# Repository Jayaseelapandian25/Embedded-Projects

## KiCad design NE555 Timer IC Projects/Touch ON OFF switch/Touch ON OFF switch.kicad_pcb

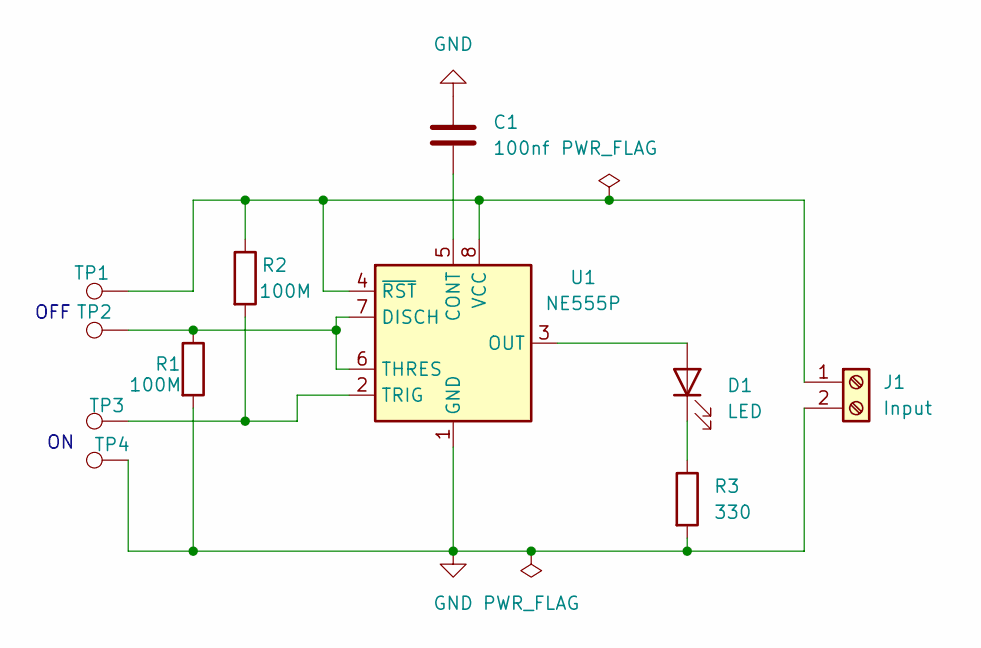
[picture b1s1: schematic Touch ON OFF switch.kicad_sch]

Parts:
C1: 100nf; C_Disc_D5.0mm_W2.5mm_P5.00mm
D1: LED; LED_D5.0mm
J1: Input; TerminalBlock_MaiXu_MX126-5.0-02P_1x02_P5.00mm
R1, R2: 100M; R_Axial_DIN0207_L6.3mm_D2.5mm_P7.62mm_Horizontal
R3: 330; R_Axial_DIN0207_L6.3mm_D2.5mm_P7.62mm_Horizontal
TP1, TP2, TP3, TP4: TestPoint; TestPoint_Pad_D4.0mm
U1: NE555P; DIP-8_W7.62mm

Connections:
GND: C1.1, J1.2, R1.2, R3.2, TP4.1 (1_1), U1.1 (GND)
unnamed: D1.2 (A), U1.3 (OUT)
unnamed: D1.1 (K), R3.1
unnamed: J1.1, R2.1, TP1.1 (1_1), U1.4 (~RST), U1.8 (VCC)
unnamed: C1.2, U1.5 (CONT)
unnamed: R1.1, TP2.1 (1_1), U1.6 (THRES), U1.7 (DISCH)
unnamed: R2.2, TP3.1 (1_1), U1.2 (TRIG)

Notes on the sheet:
OFF

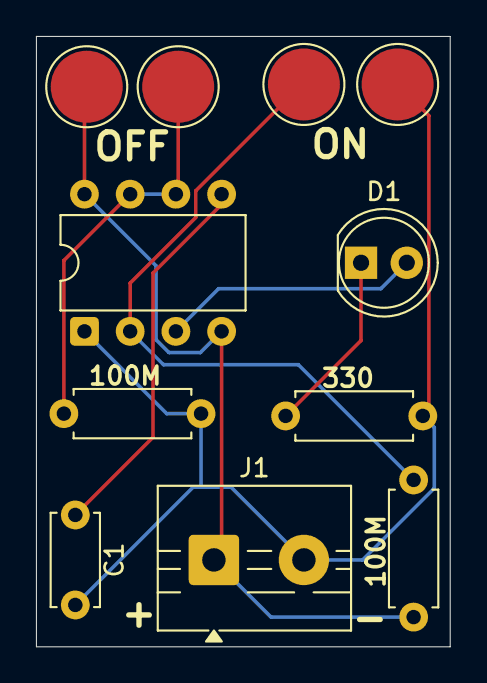
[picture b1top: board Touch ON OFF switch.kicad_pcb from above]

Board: 2 copper layers, 23.0 x 33.9 mm, 11 parts (0 on the bottom side), 7 nets.

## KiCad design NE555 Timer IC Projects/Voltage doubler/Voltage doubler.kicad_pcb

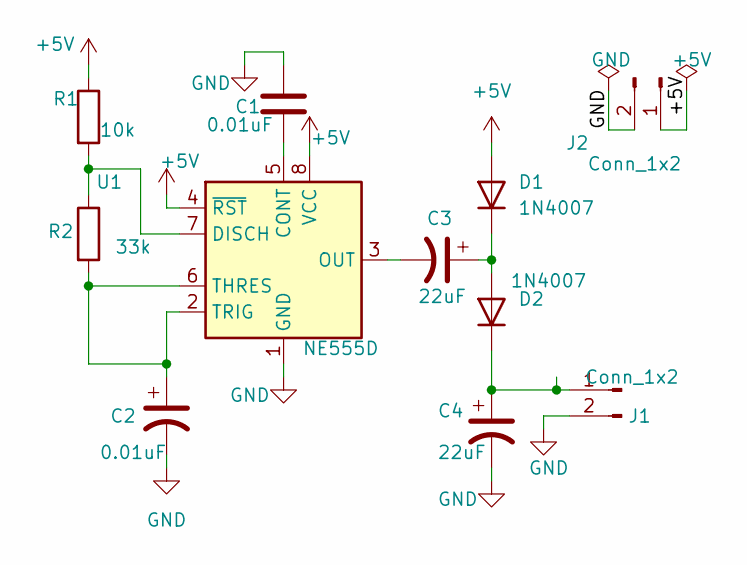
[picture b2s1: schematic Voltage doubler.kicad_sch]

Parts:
C1, C2: 0.01uF; C_Disc_D3.0mm_W1.6mm_P2.50mm
C3, C4: 22uF; C_Radial_D4.0mm_H5.0mm_P1.50mm
D1, D2: 1N4007; D_5W_P10.16mm_Horizontal
J1, J2: Conn_1x2; PinHeader_1x02_P1.00mm_Horizontal
R1: 10k; R_Axial_DIN0204_L3.6mm_D1.6mm_P5.08mm_Horizontal
R2: 33k; R_Axial_DIN0204_L3.6mm_D1.6mm_P5.08mm_Horizontal
U1: NE555D; SO-8_3.9x4.9mm_P1.27mm

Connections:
+5V: D1.2 (A), J2.1, R1.1, U1.4 (~RST), U1.8 (VCC)
GND: C1.1, C2.2, C4.2, J1.2, J2.2, U1.1 (GND)
unnamed: C3.1, D1.1 (K), D2.2 (A)
unnamed: C4.1, D2.1 (K), J1.1
unnamed: C1.2, U1.5 (CONT)
unnamed: R1.2, R2.1, U1.7 (DISCH)
unnamed: C3.2, U1.3 (OUT)
unnamed: C2.1, R2.2, U1.2 (TRIG), U1.6 (THRES)

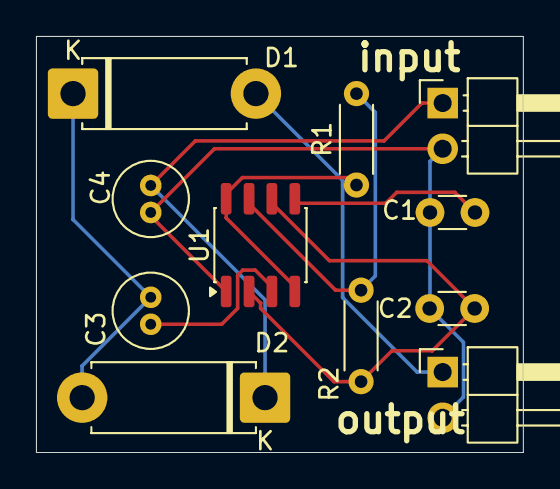
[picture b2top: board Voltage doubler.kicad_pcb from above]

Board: 2 copper layers, 27.1 x 23.1 mm, 11 parts (0 on the bottom side), 8 nets.

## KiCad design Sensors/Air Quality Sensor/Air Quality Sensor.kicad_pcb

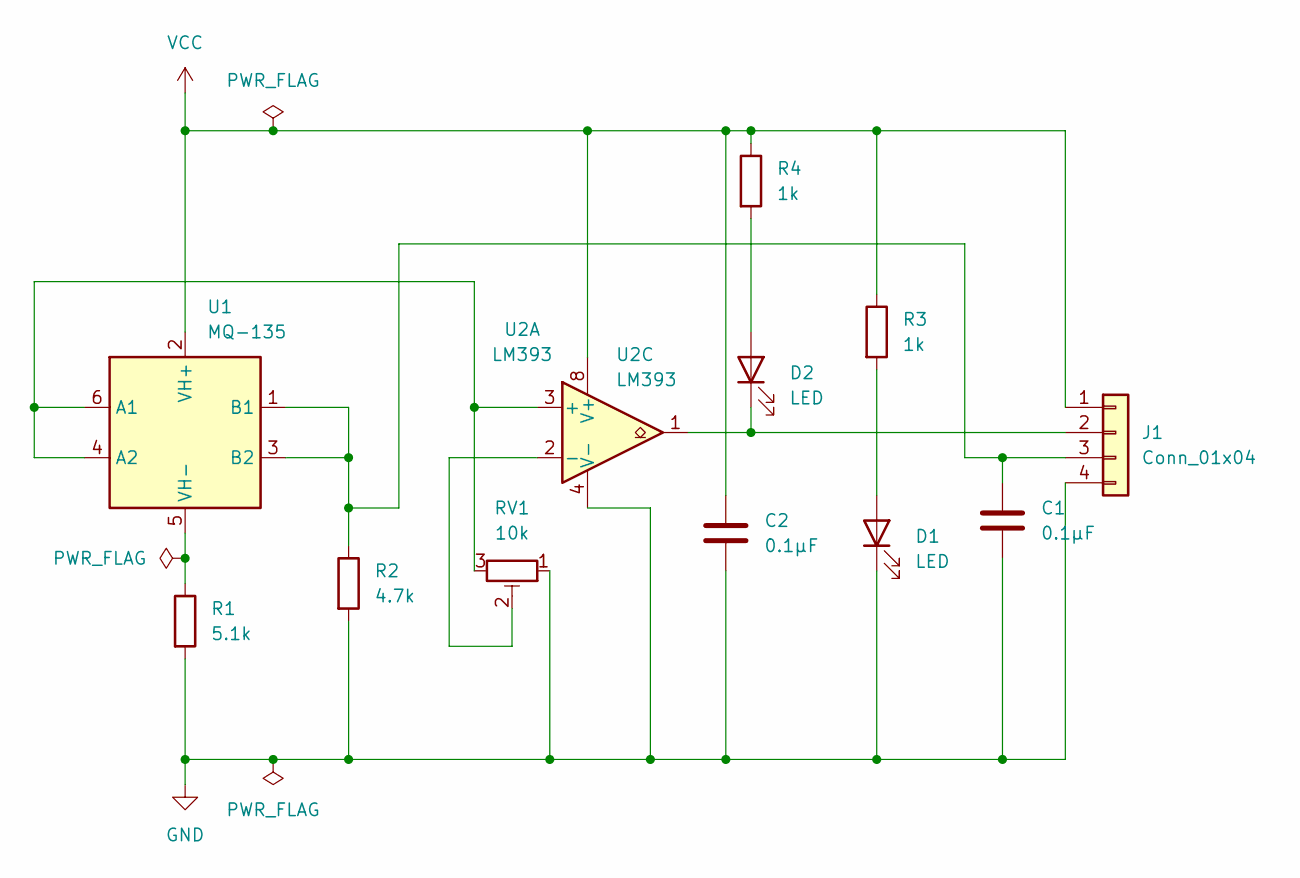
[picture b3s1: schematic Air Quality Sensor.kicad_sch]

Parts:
C1, C2: 0.1µF; C_0805_2012Metric_Pad1.18x1.45mm_HandSolder
D1, D2: LED; LED_0805_2012Metric_Pad1.15x1.40mm_HandSolder
J1: Conn_01x04; PinHeader_1x04_P2.54mm_Vertical
R1: 5.1k; R_0805_2012Metric_Pad1.20x1.40mm_HandSolder
R2: 4.7k; R_0805_2012Metric_Pad1.20x1.40mm_HandSolder
R3, R4: 1k; R_0805_2012Metric_Pad1.20x1.40mm_HandSolder
RV1: 10k; Potentiometer_Bourns_3214X_Vertical
U1: MQ-135; MQ-6
U2: LM393; SOIC-8_3.9x4.9mm_P1.27mm

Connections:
GND: C1.2, C2.2, D1.1 (K), J1.4, R1.2, R2.2, RV1.1, U2.4 (V-)
unnamed: D1.2 (A), R3.2
unnamed: D2.2 (A), R4.2
unnamed: D2.1 (K), J1.2, U2.1
unnamed: C1.1, J1.3, R2.1, U1.1 (B1), U1.3 (B2)
unnamed: RV1.3, U1.4 (A2), U1.6 (A1), U2.3 (+)
unnamed: R1.1, U1.5 (VH-)
unnamed: RV1.2, U2.2 (-)
VCC: C2.1, J1.1, R3.1, R4.1, U1.2 (VH+), U2.8 (V+)

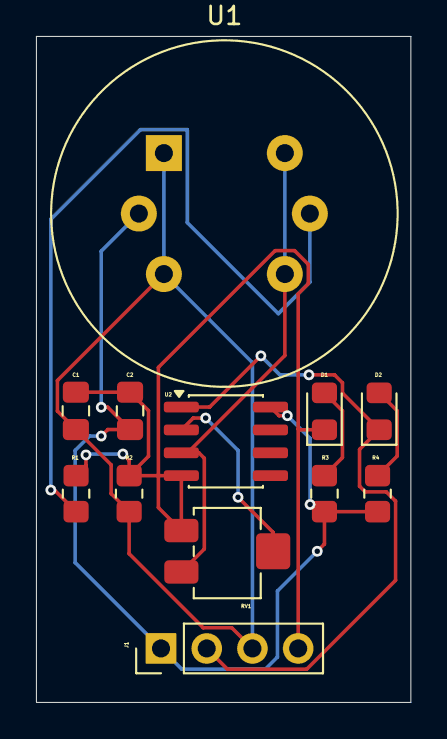
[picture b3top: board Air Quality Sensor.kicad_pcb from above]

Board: 2 copper layers, 20.8 x 37.0 mm, 12 parts (0 on the bottom side), 9 nets.

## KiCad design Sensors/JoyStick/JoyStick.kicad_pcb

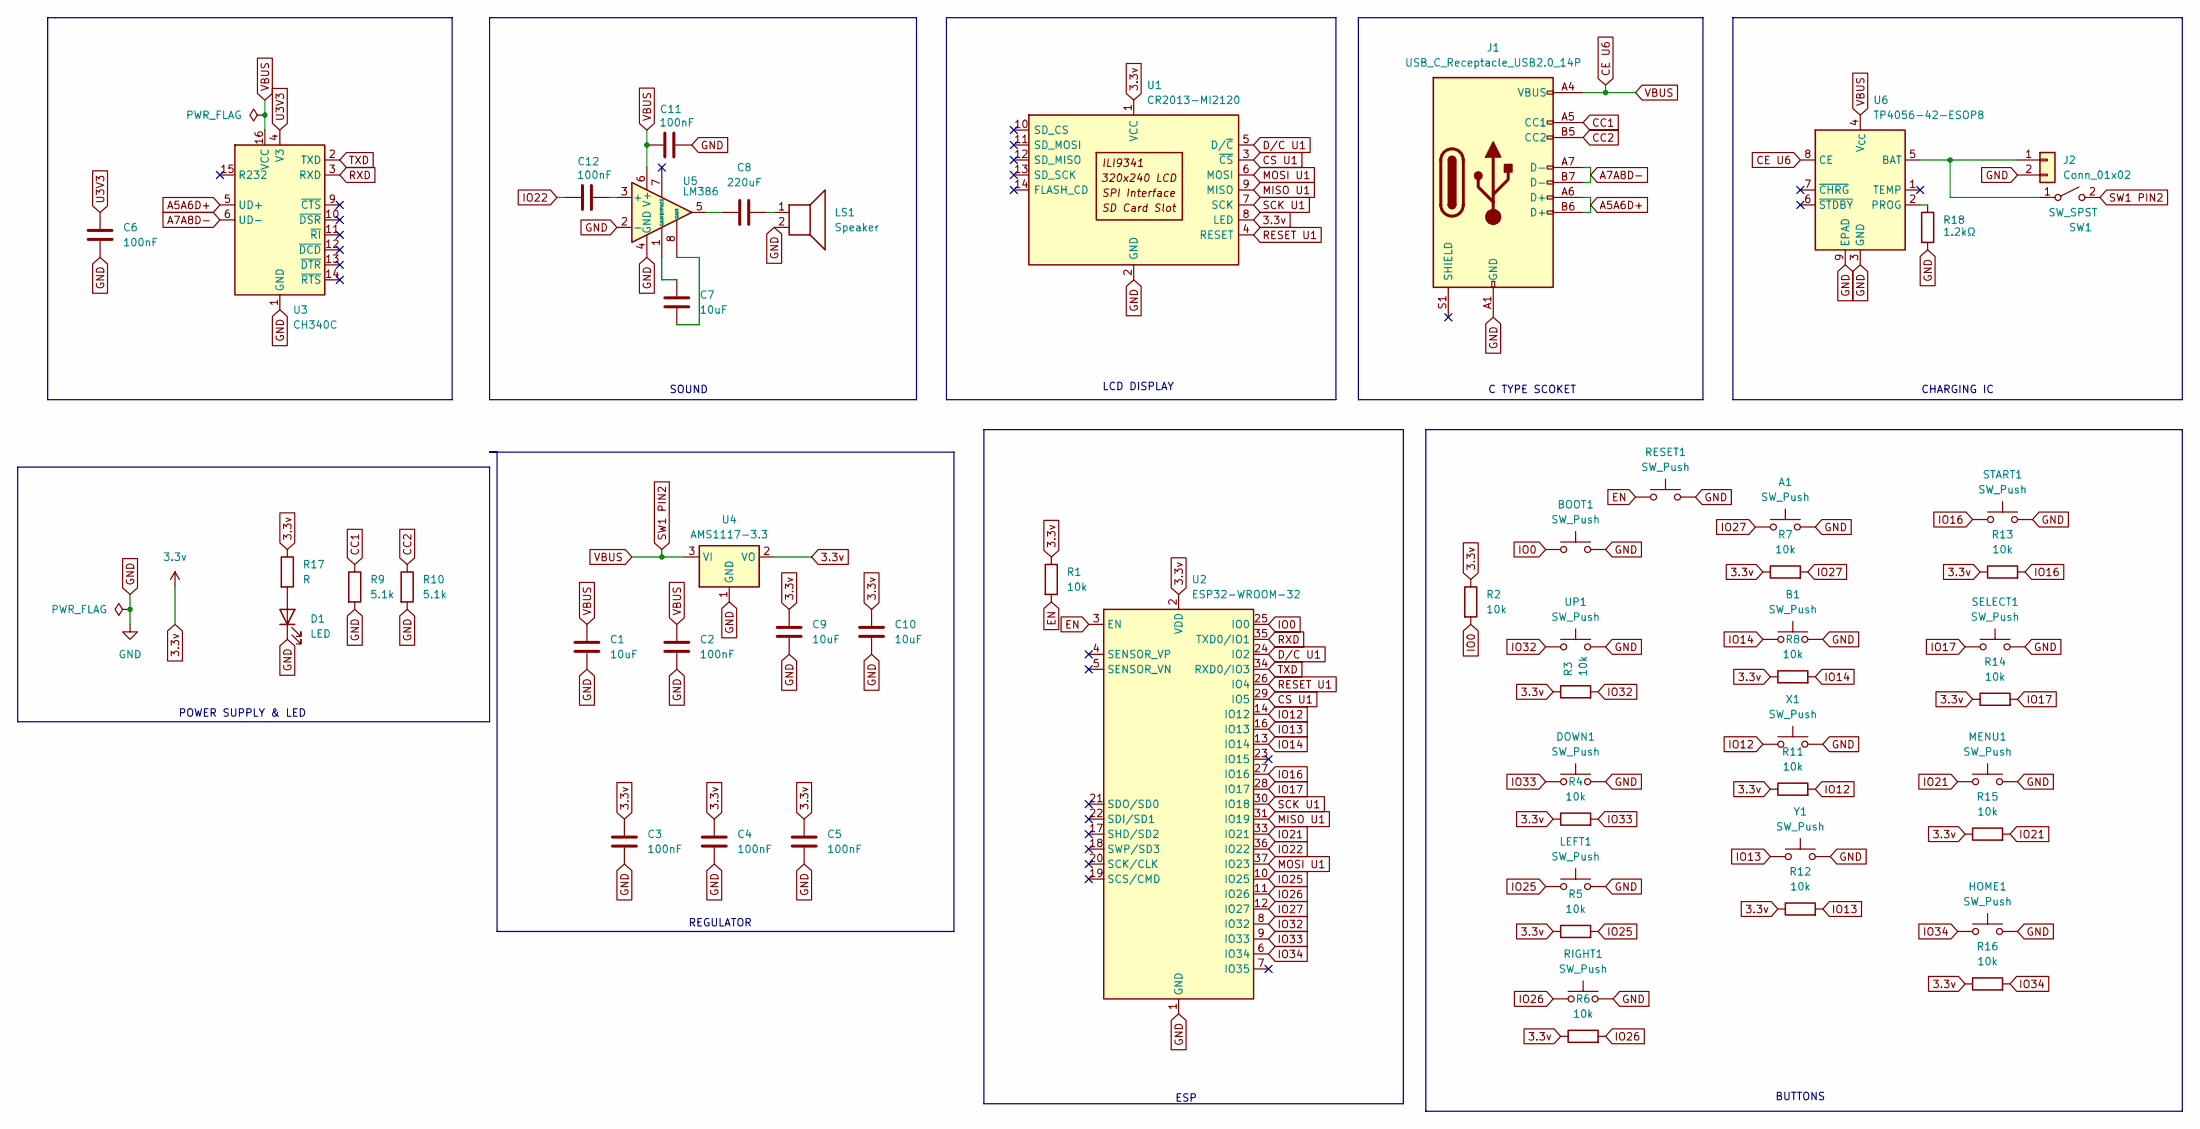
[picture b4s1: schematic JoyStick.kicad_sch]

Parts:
A1: SW_Push; SW_SPST_TL3342
B1: SW_Push; SW_SPST_TL3342
BOOT1: SW_Push; SW_SPST_TL3342
C1, C7, C9, C10: 10uF; C_0805_2012Metric
C2, C3, C4, C5, C6, C11, C12: 100nF; C_0805_2012Metric
C8: 220uF; C_0805_2012Metric
D1: LED; LED_0805_2012Metric
DOWN1: SW_Push; SW_SPST_TL3342
HOME1: SW_Push; SW_SPST_TL3342
J1: USB_C_Receptacle_USB2.0_14P; USB_C_Receptacle_HRO_TYPE-C-31-M-12
J2: Conn_01x02; JST_PH_S2B-PH-K_1x02_P2.00mm_Horizontal
LEFT1: SW_Push; SW_SPST_TL3342
LS1: Speaker; JST_PH_S2B-PH-K_1x02_P2.00mm_Horizontal
MENU1: SW_Push; SW_SPST_TL3342
R1, R2, R3, R4, R5, R6, R7, R8, R11, R12, R13, R14, R15, R16: 10k; R_0805_2012Metric
R9, R10: 5.1k; R_0805_2012Metric
R17: R; R_0805_2012Metric
R18: 1.2kΩ; R_0805_2012Metric
RESET1: SW_Push; SW_SPST_TL3342
RIGHT1: SW_Push; SW_SPST_TL3342
SELECT1: SW_Push; SW_SPST_TL3342
START1: SW_Push; SW_SPST_TL3342
SW1: SW_SPST; SW_SPST_TL3342
U1: CR2013-MI2120
U2: ESP32-WROOM-32
U3: CH340C; SOIC-16_3.9x9.9mm_P1.27mm
U4: AMS1117-3.3; SOT-223-3_TabPin2
U5: LM386; SOIC-8_3.9x4.9mm_P1.27mm
U6: TP4056-42-ESOP8; SOIC-8-1EP_3.9x4.9mm_P1.27mm_EP2.41x3.3mm_ThermalVias
UP1: SW_Push; SW_SPST_TL3342
X1: SW_Push; SW_SPST_TL3342
Y1: SW_Push; SW_SPST_TL3342

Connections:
3.3v: C3.1, C4.1, C5.1, C9.1, C10.1, R1.1, R2.1, R3.1, R4.1, R5.1, R6.1, R7.1, R8.1, R11.1, R12.1, R13.1, R14.1, R15.1, R16.1, R17.1, U1.1 (VCC), U1.8 (LED), U2.2 (VDD), U4.2 (VO)
A5A6D+: J1.A6 (D+), J1.B6 (D+), U3.5 (UD+)
A7A8D-: J1.A7 (D-), J1.B7 (D-), U3.6 (UD-)
CC1: J1.A5 (CC1), R9.1
CC2: J1.B5 (CC2), R10.1
CE U6: C1.1, C2.1, C11.1, J1.A4 (VBUS), J1.A9 (VBUS), J1.B4 (VBUS), J1.B9 (VBUS), SW1.2 (B), U3.16 (VCC), U4.3 (VI), U5.6 (V+), U6.4 (V_{CC}), U6.8 (CE)
CS U1: U1.3 (~CS), U2.29 (IO5)
D/C U1: U1.5 (D/~C), U2.24 (IO2)
EN: R1.2, RESET1.1, U2.3 (EN)
GND: A1.2, B1.2, BOOT1.2, C1.2, C2.2, C3.2, C4.2, C5.2, C6.2, C9.2, C10.2, C11.2, D1.1 (K), DOWN1.2, HOME1.2, J1.A1 (GND), J1.A12 (GND), J1.B1 (GND), J1.B12 (GND), J2.2, LEFT1.2, LS1.2, MENU1.2, R9.2, R10.2, R18.2, RESET1.2, RIGHT1.2, SELECT1.2, START1.2, U1.2 (GND), U2.1 (GND), U2.15 (GND), U2.38 (GND), U2.39 (GND), U3.1 (GND), U4.1 (GND), U5.2 (-), U5.4 (GND), U6.3 (GND), U6.9 (EPAD), UP1.2, X1.2, Y1.2
IO0: BOOT1.1, R2.2, U2.25 (IO0)
IO12: R11.2, U2.14 (IO12), X1.1
IO13: R12.2, U2.16 (IO13), Y1.1
IO14: B1.1, R8.2, U2.13 (IO14)
IO16: R13.2, START1.1, U2.27 (IO16)
IO17: R14.2, SELECT1.1, U2.28 (IO17)
IO21: MENU1.1, R15.2, U2.33 (IO21)
IO22: C12.1, U2.36 (IO22)
IO25: LEFT1.1, R5.2, U2.10 (IO25)
IO26: R6.2, RIGHT1.1, U2.11 (IO26)
IO27: A1.1, R7.2, U2.12 (IO27)
IO32: R3.2, U2.8 (IO32), UP1.1
IO33: DOWN1.1, R4.2, U2.9 (IO33)
IO34: HOME1.1, R16.2, U2.6 (IO34)
MISO U1: U1.9 (MISO), U2.31 (IO19)
MOSI U1: U1.6 (MOSI), U2.37 (IO23)
unnamed: C7.1, U5.1 (GAIN)
unnamed: C7.2, U5.8 (GAIN)
unnamed: C8.1, U5.5
unnamed: C8.2, LS1.1
unnamed: D1.2 (A), R17.2
unnamed: J2.1, SW1.1 (A), U6.5 (BAT)
unnamed: C12.2, U5.3 (+)
unnamed: R18.1, U6.2 (PROG)
RESET U1: U1.4 (RESET), U2.26 (IO4)
RXD: U2.35 (TXD0/IO1), U3.3 (RXD)
SCK U1: U1.7 (SCK), U2.30 (IO18)
TXD: U2.34 (RXD0/IO3), U3.2 (TXD)
U3V3: C6.1, U3.4 (V3)

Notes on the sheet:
CHARGING IC
LCD DISPLAY
SOUND
POWER SUPPLY & LED
BUTTONS
C TYPE SCOKET
ESP
REGULATOR

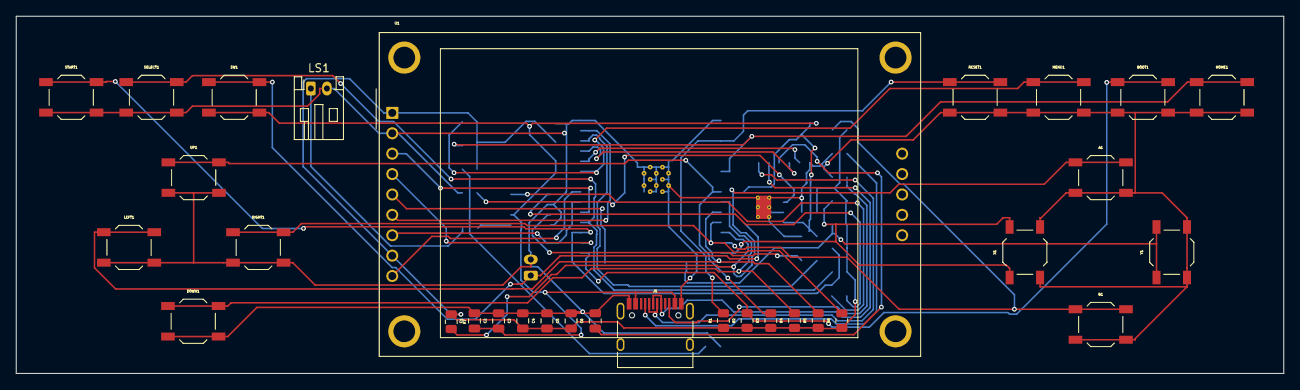
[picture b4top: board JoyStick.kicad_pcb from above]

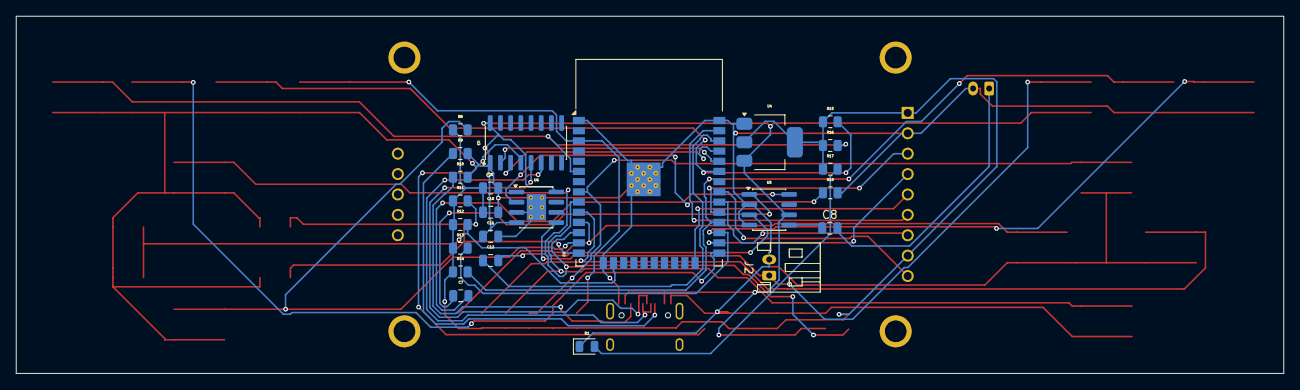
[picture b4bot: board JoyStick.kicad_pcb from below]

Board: 2 copper layers, 157.9 x 44.5 mm, 55 parts (24 on the bottom side), 39 nets.

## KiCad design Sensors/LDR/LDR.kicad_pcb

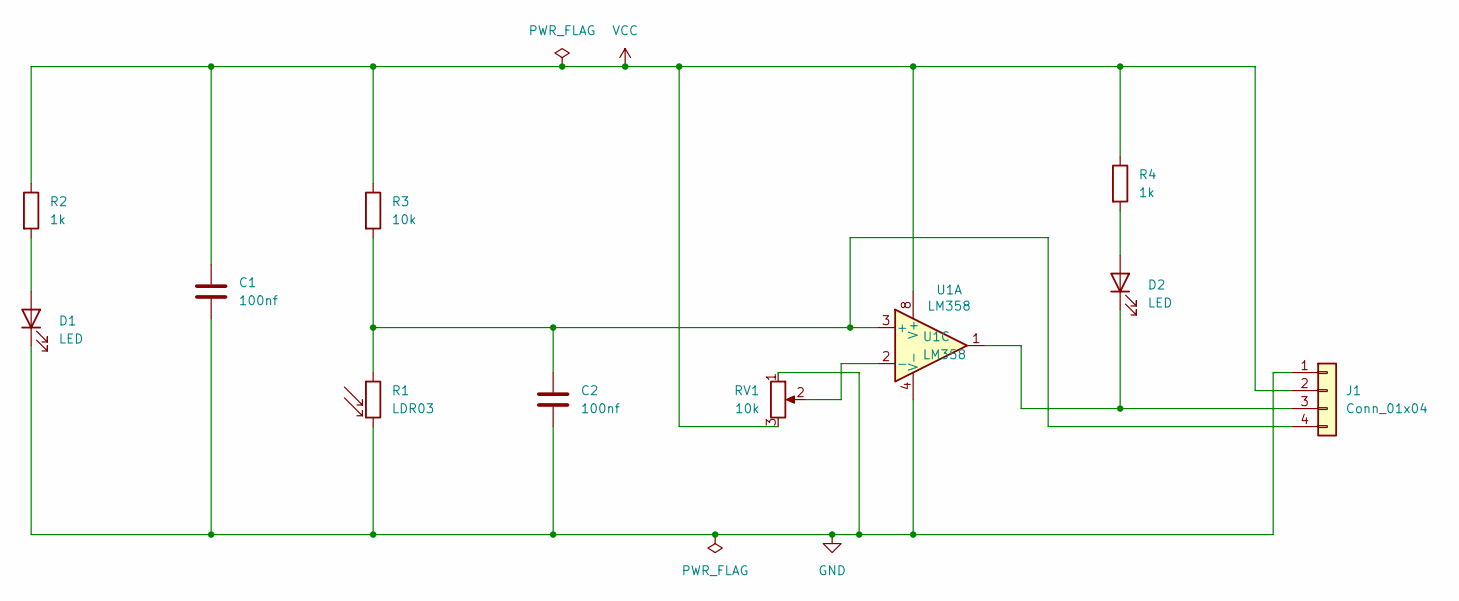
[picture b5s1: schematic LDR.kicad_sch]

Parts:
C1, C2: 100nf; C_0805_2012Metric_Pad1.18x1.45mm_HandSolder
D1, D2: LED; LED_0805_2012Metric_Pad1.15x1.40mm_HandSolder
J1: Conn_01x04; PinHeader_1x04_P2.54mm_Vertical
R1: LDR03; R_LDR_10x8.5mm_P7.6mm_Vertical
R2, R4: 1k; R_0805_2012Metric_Pad1.20x1.40mm_HandSolder
R3: 10k; R_0805_2012Metric_Pad1.20x1.40mm_HandSolder
RV1: 10k; Potentiometer_Bourns_3296W_Vertical
U1: LM358; DIP-8_W7.62mm

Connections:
GND: C1.2, C2.2, D1.1 (K), J1.1, R1.2, RV1.1, U1.4 (V-)
unnamed: D1.2 (A), R2.2
unnamed: D2.2 (A), R4.2
unnamed: D2.1 (K), J1.3, U1.1
unnamed: C2.1, J1.4, R1.1, R3.2, U1.3 (+)
unnamed: RV1.2, U1.2 (-)
VCC: C1.1, J1.2, R2.1, R3.1, R4.1, RV1.3, U1.8 (V+)

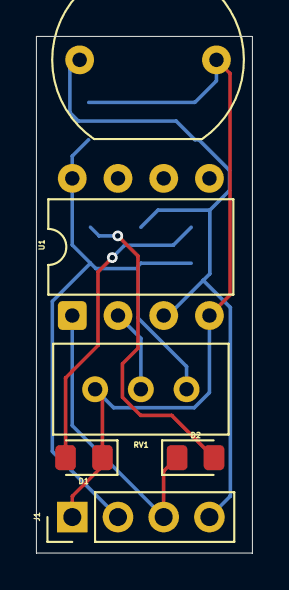
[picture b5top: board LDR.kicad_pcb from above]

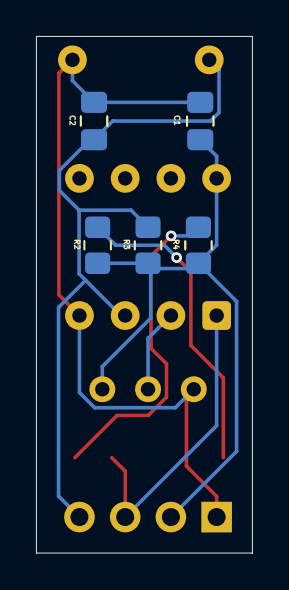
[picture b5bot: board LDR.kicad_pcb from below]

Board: 2 copper layers, 12.0 x 28.7 mm, 11 parts (5 on the bottom side), 7 nets.

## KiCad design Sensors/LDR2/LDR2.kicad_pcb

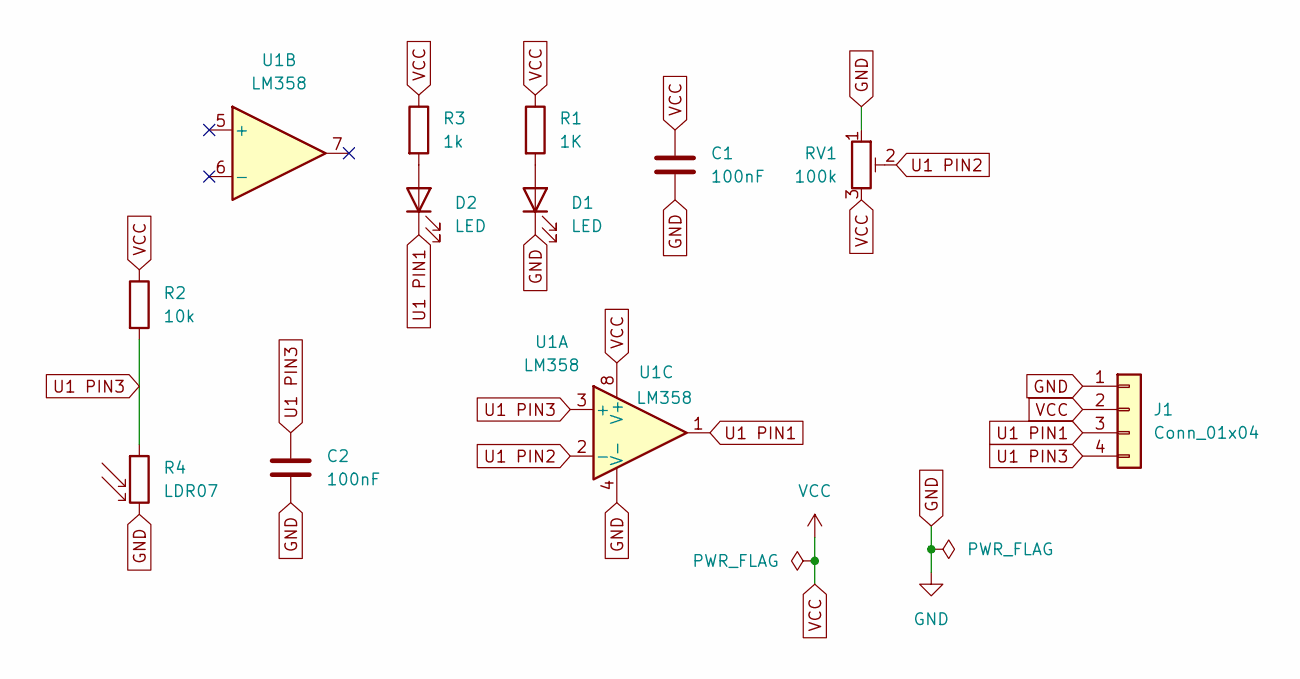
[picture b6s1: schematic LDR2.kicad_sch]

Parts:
C1, C2: 100nF; C_0805_2012Metric_Pad1.18x1.45mm_HandSolder
D1, D2: LED; LED_0805_2012Metric_Pad1.15x1.40mm_HandSolder
J1: Conn_01x04; PinHeader_1x04_P2.54mm_Vertical
R1: 1K; R_0805_2012Metric_Pad1.20x1.40mm_HandSolder
R2: 10k; R_0805_2012Metric_Pad1.20x1.40mm_HandSolder
R3: 1k; R_0805_2012Metric_Pad1.20x1.40mm_HandSolder
R4: LDR07; R_LDR_5.1x4.3mm_P3.4mm_Vertical
RV1: 100k; Potentiometer_Bourns_3296W_Vertical
U1: LM358; DIP-8_W7.62mm

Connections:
GND: C1.2, C2.2, D1.1 (K), J1.1, R4.2, RV1.1, U1.4 (V-)
unnamed: D1.2 (A), R1.2
unnamed: D2.2 (A), R3.2
U1 PIN1: D2.1 (K), J1.3, U1.1
U1 PIN2: RV1.2, U1.2 (-)
U1 PIN3: C2.1, J1.4, R2.2, R4.1, U1.3 (+)
VCC: C1.1, J1.2, R1.1, R2.1, R3.1, RV1.3, U1.8 (V+)

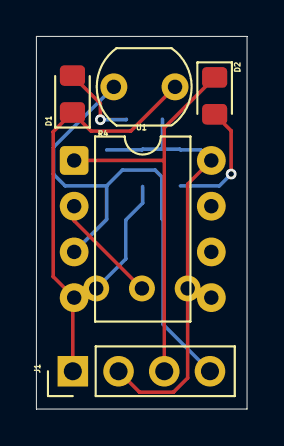
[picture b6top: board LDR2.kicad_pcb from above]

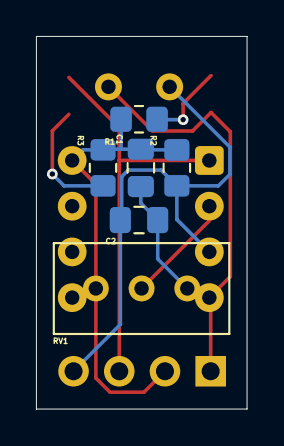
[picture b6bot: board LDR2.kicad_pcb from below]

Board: 2 copper layers, 11.7 x 20.7 mm, 11 parts (6 on the bottom side), 7 nets.

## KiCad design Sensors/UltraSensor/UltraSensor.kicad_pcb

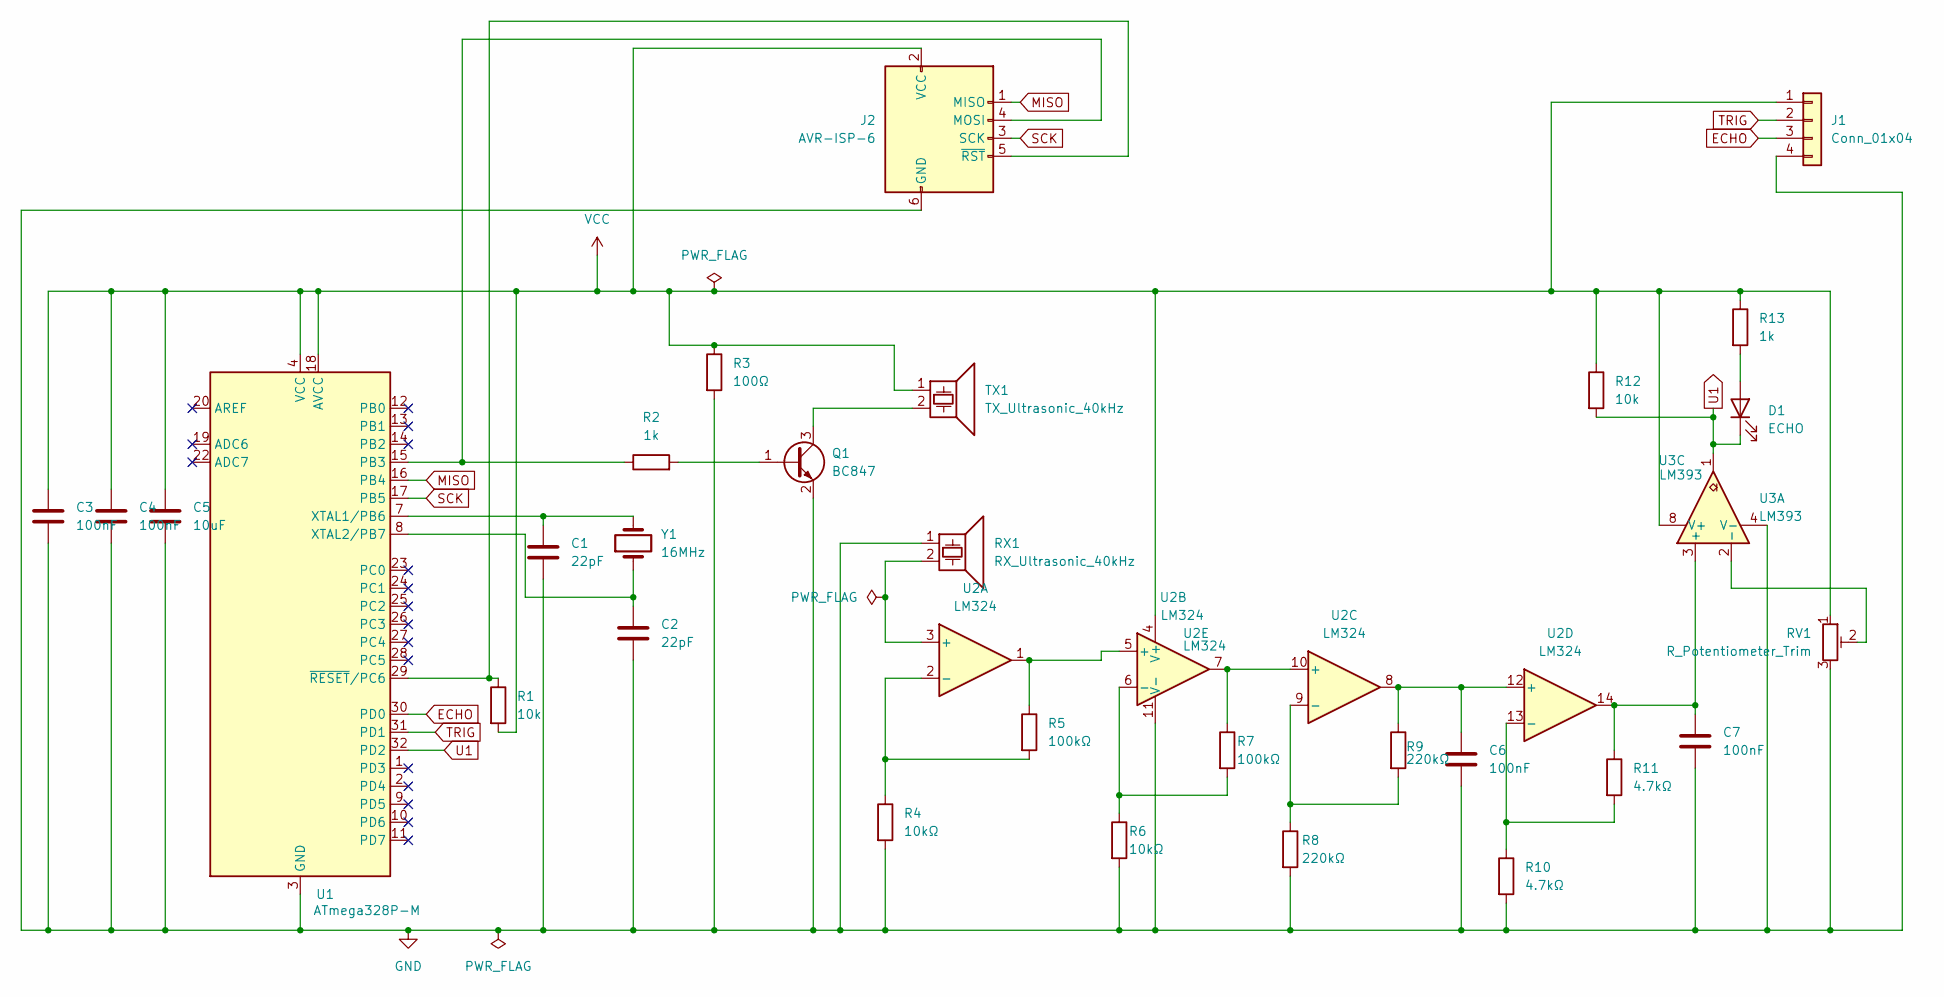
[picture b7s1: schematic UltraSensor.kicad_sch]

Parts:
C1, C2: 22pF; C_0805_2012Metric_Pad1.18x1.45mm_HandSolder
C3, C4, C6, C7: 100nF; C_0805_2012Metric_Pad1.18x1.45mm_HandSolder
C5: 10uF; C_0805_2012Metric_Pad1.18x1.45mm_HandSolder
D1: ECHO; LED_0805_2012Metric
J1: Conn_01x04; PinHeader_1x04_P2.54mm_Vertical
J2: AVR-ISP-6; PinHeader_2x03_P2.54mm_Vertical
Q1: BC847; SOT-23
R1, R12: 10k; R_0805_2012Metric_Pad1.20x1.40mm_HandSolder
R2, R13: 1k; R_0805_2012Metric_Pad1.20x1.40mm_HandSolder
R3: 100Ω; R_0805_2012Metric_Pad1.20x1.40mm_HandSolder
R4, R6: 10kΩ; R_0805_2012Metric_Pad1.20x1.40mm_HandSolder
R5, R7: 100kΩ; R_0805_2012Metric_Pad1.20x1.40mm_HandSolder
R8, R9: 220kΩ; R_0805_2012Metric_Pad1.20x1.40mm_HandSolder
R10, R11: 4.7kΩ; R_0805_2012Metric_Pad1.20x1.40mm_HandSolder
RV1: R_Potentiometer_Trim; Potentiometer_ACP_CA6-VSMD_Vertical
RX1: RX_Ultrasonic_40kHz; Buzzer_12x9.5RM7.6
TX1: TX_Ultrasonic_40kHz; Buzzer_12x9.5RM7.6
U1: ATmega328P-M; QFN-32-1EP_5x5mm_P0.5mm_EP3.1x3.1mm
U2: LM324; SOIC-14_3.9x8.7mm_P1.27mm
U3: LM393; SOIC-8_3.9x4.9mm_P1.27mm
Y1: 16MHz; Crystal_SMD_3225-4Pin_3.2x2.5mm_HandSoldering

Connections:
ECHO: J1.3, U1.30 (PD0)
GND: C1.2, C2.2, C3.2, C4.2, C5.2, C6.2, C7.2, J1.4, J2.6 (GND), Q1.2 (E), R3.2, R4.2, R6.2, R8.2, R10.2, RV1.3, RX1.1, U1.3 (GND), U1.5 (GND), U1.21 (GND), U1.33 (GND), U2.11 (V-), U3.4 (V-)
MISO: J2.1 (MISO), U1.16 (PB4)
unnamed: D1.2 (A), R13.2
unnamed: J2.4 (MOSI), R2.1, U1.15 (PB3)
unnamed: J2.5 (~RST), R1.1, U1.29 (~RESET/PC6)
unnamed: Q1.1 (B), R2.2
unnamed: Q1.3 (C), TX1.2
unnamed: C1.1, U1.7 (XTAL1/PB6), Y1.2
unnamed: C2.1, U1.8 (XTAL2/PB7), Y1.1
unnamed: RX1.2, U2.3 (+)
unnamed: R4.1, R5.2, U2.2 (-)
unnamed: R5.1, U2.1, U2.5 (+)
unnamed: R6.1, R7.2, U2.6 (-)
unnamed: R7.1, U2.7, U2.10 (+)
unnamed: R8.1, R9.2, U2.9 (-)
unnamed: C6.1, R9.1, U2.8, U2.12 (+)
unnamed: R10.1, R11.2, U2.13 (-)
unnamed: C7.1, R11.1, U2.14, U3.3 (+)
unnamed: RV1.2, U3.2 (-)
SCK: J2.3 (SCK), U1.17 (PB5)
TRIG: J1.2, U1.31 (PD1)
U1: D1.1 (K), R12.2, U1.32 (PD2), U3.1
VCC: C3.1, C4.1, C5.1, J1.1, J2.2 (VCC), R1.2, R3.1, R12.1, R13.1, RV1.1, TX1.1, U1.4 (VCC), U1.6 (VCC), U1.18 (AVCC), U2.4 (V+), U3.8 (V+)

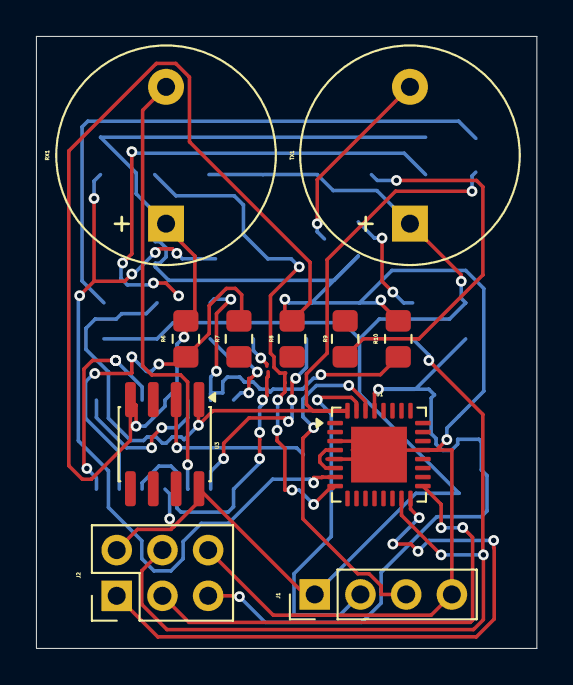
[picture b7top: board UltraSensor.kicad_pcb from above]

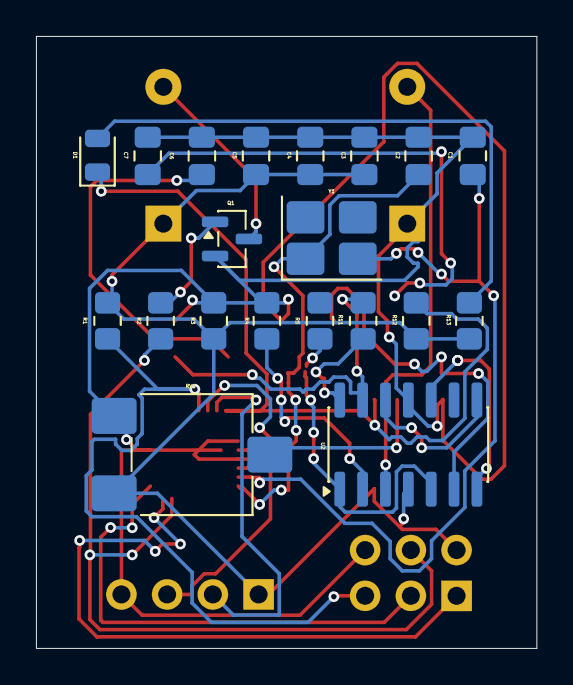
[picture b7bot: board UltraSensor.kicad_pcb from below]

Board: 2 copper layers, 27.8 x 34.0 mm, 31 parts (20 on the bottom side), 24 nets.

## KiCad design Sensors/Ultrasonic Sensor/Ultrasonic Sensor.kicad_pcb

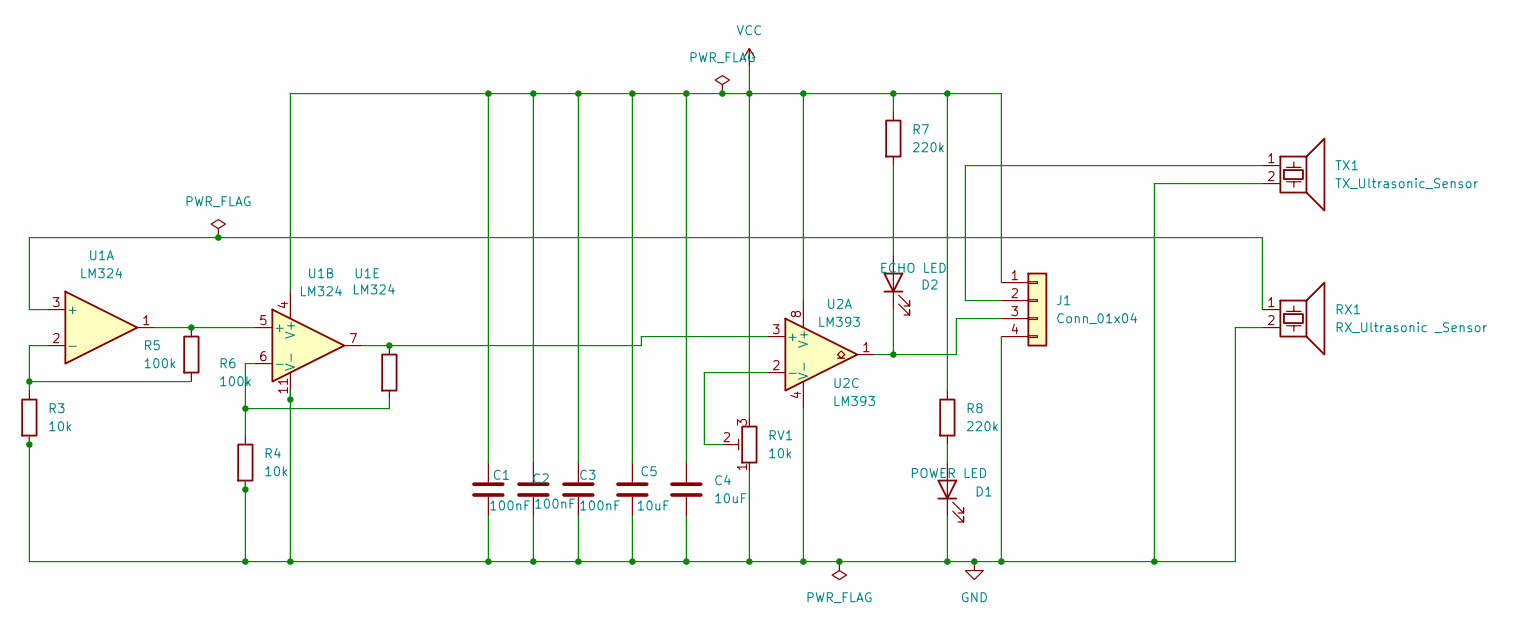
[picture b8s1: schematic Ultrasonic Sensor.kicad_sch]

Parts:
C1, C2, C3: 100nF; C_0805_2012Metric_Pad1.18x1.45mm_HandSolder
C4, C5: 10uF; C_0805_2012Metric_Pad1.18x1.45mm_HandSolder
D1: POWER LED; LED_0805_2012Metric_Pad1.15x1.40mm_HandSolder
D2: ECHO LED; LED_0805_2012Metric_Pad1.15x1.40mm_HandSolder
J1: Conn_01x04; PinHeader_1x04_P2.54mm_Vertical
R3, R4: 10k; R_0805_2012Metric_Pad1.20x1.40mm_HandSolder
R5, R6: 100k; R_0805_2012Metric_Pad1.20x1.40mm_HandSolder
R7, R8: 220k; R_0805_2012Metric_Pad1.20x1.40mm_HandSolder
RV1: 10k; Potentiometer_Bourns_3214X_Vertical
RX1: RX_Ultrasonic _Sensor; Buzzer_12x9.5RM7.6
TX1: TX_Ultrasonic_Sensor; Buzzer_12x9.5RM7.6
U1: LM324; SOIC-14_3.9x8.7mm_P1.27mm
U2: LM393; SOIC-8_3.9x4.9mm_P1.27mm

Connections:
GND: C1.2, C2.2, C3.2, C4.2, C5.2, D1.1 (K), J1.4, R3.2, R4.2, RV1.1, RX1.2, TX1.2, U1.11 (V-), U2.4 (V-)
unnamed: D1.2 (A), R8.2
unnamed: D2.2 (A), R7.2
unnamed: D2.1 (K), J1.3, U2.1
unnamed: J1.2, TX1.1
unnamed: RX1.1, U1.3 (+)
unnamed: R3.1, R5.2, U1.2 (-)
unnamed: R5.1, U1.1, U1.5 (+)
unnamed: R4.1, R6.2, U1.6 (-)
unnamed: R6.1, U1.7, U2.3 (+)
unnamed: RV1.2, U2.2 (-)
VCC: C1.1, C2.1, C3.1, C4.1, C5.1, J1.1, R7.1, R8.1, RV1.3, U1.4 (V+), U2.8 (V+)

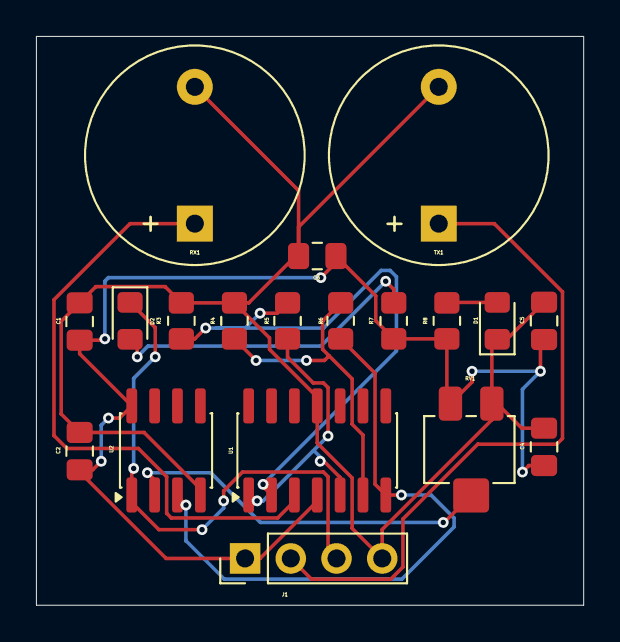
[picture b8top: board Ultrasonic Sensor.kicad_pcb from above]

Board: 2 copper layers, 30.4 x 31.6 mm, 19 parts (0 on the bottom side), 12 nets.
